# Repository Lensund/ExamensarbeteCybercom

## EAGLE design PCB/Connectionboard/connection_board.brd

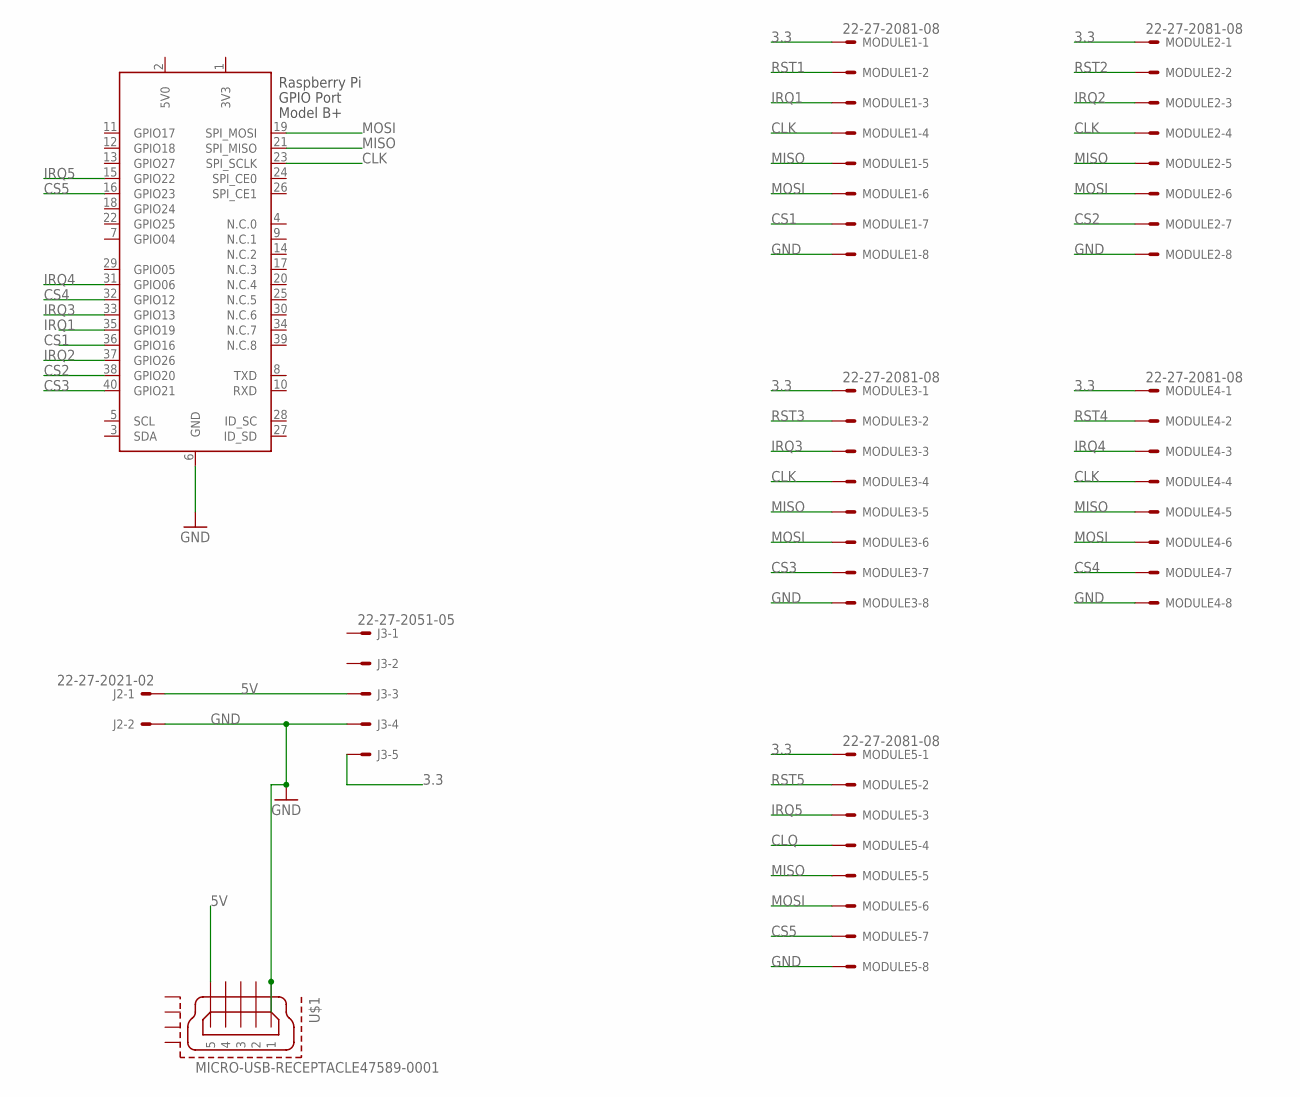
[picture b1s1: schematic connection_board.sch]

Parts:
J2: 22-27-2021-02; 6410-02
J3: 22-27-2051-05; 6410-05
MODULE1, MODULE2, MODULE3, MODULE4, MODULE5: 22-27-2081-08; 6410-08
U$1: MICRO-USB-RECEPTACLE47589-0001; 47589-0001
X1: RASPI_BOARD_B+_E0; RASPI_BOARD_B+_EDGES_0DRILL

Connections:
3.3: J3.5, MODULE1.1, MODULE2.1, MODULE3.1, MODULE4.1, MODULE5.1
3V3: X1.1 (3V3)
5V: J2.1, J3.3, U$1.5
5V0: X1.2 (5V0)
CLK: MODULE1.4, MODULE2.4, MODULE3.4, MODULE4.4, X1.23 (SPI_SCLK)
CLQ: MODULE5.4
CS1: MODULE1.7, X1.36 (GPIO16)
CS2: MODULE2.7, X1.38 (GPIO20)
CS3: MODULE3.7, X1.40 (GPIO21)
CS4: MODULE4.7, X1.32 (GPIO12)
CS5: MODULE5.7, X1.16 (GPIO23)
GND: J2.2, J3.4, MODULE1.8, MODULE2.8, MODULE3.8, MODULE4.8, MODULE5.8, U$1.1, X1.6 (GND)
IRQ1: MODULE1.3, X1.35 (GPIO19)
IRQ2: MODULE2.3, X1.37 (GPIO26)
IRQ3: MODULE3.3, X1.33 (GPIO13)
IRQ4: MODULE4.3, X1.31 (GPIO06)
IRQ5: MODULE5.3, X1.15 (GPIO22)
MISO: MODULE1.5, MODULE2.5, MODULE3.5, MODULE4.5, MODULE5.5, X1.21 (SPI_MISO)
MOSI: MODULE1.6, MODULE2.6, MODULE3.6, MODULE4.6, MODULE5.6, X1.19 (SPI_MOSI)
RST1: MODULE1.2
RST2: MODULE2.2
RST3: MODULE3.2
RST4: MODULE4.2
RST5: MODULE5.2

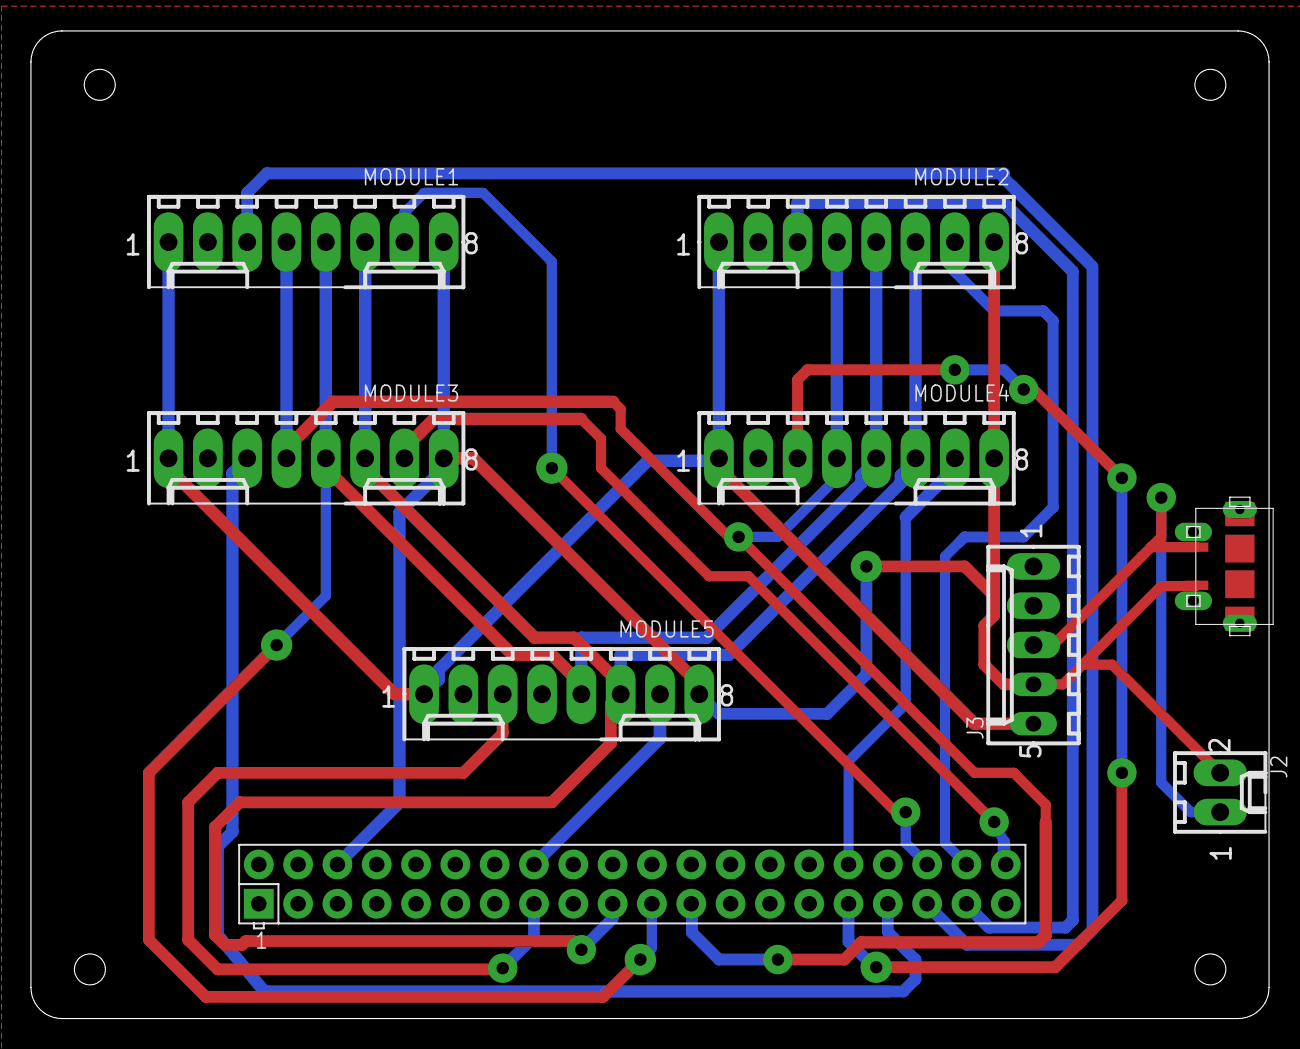
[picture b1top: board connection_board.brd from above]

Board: 2 copper layers, 80.0 x 63.8 mm, 9 parts (0 on the bottom side), 16 nets.

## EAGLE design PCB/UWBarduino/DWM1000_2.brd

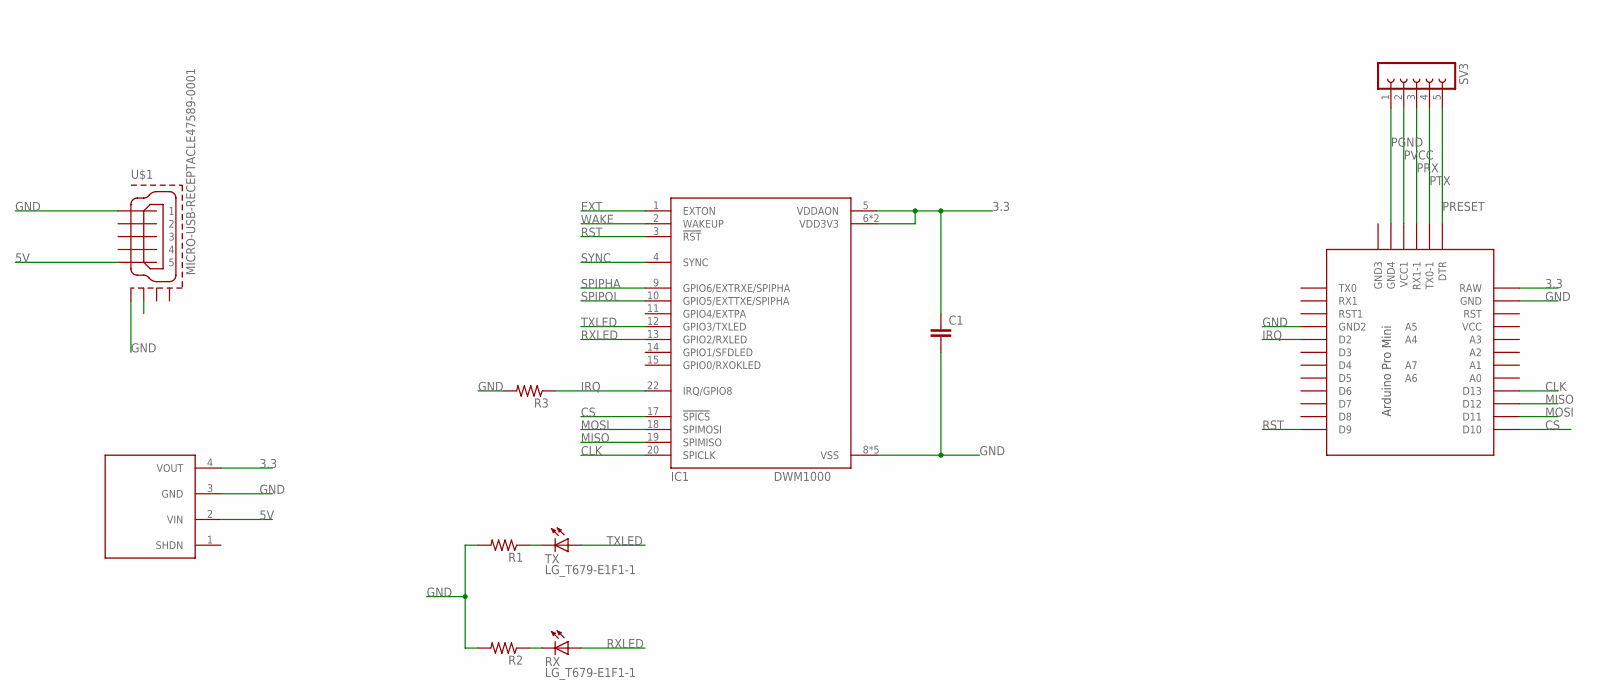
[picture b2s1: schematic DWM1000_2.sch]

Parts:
C1: CC1206; C1206
IC1: DWM1000
R1, R2, R3: R-US_M0805; M0805
RX: LG_T679-E1F1-1; PLCC2
SV3: FE05-1
TX: LG_T679-E1F1-1; PLCC2
U$1: MICRO-USB-RECEPTACLE47589-0001; 47589-0001
U$2: PRO-MINI-2
U$3: D24V5F3

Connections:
3.3: C1.1, IC1.5 (VDDAON), IC1.6 (VDD3V3), IC1.7 (VDD3V3), U$2.RAW, U$3.4 (VOUT)
5V: U$1.5, U$3.2 (VIN)
CLK: IC1.20 (SPICLK), U$2.D13
CS: IC1.17 (!SPICS), U$2.D10
EXT: IC1.1 (EXTON)
GND: C1.2, IC1.8 (VSS), IC1.16 (VSS), IC1.21 (VSS), IC1.23 (VSS), IC1.24 (VSS), R1.2, R2.2, R3.2, U$1.1, U$1.CASING1 (GND1), U$2.GND, U$2.GND1 (GND2), U$3.3 (GND)
IRQ: IC1.22 (IRQ/GPIO8), R3.1, U$2.D2
MISO: IC1.19 (SPIMISO), U$2.D12
MOSI: IC1.18 (SPIMOSI), U$2.D11
unnamed: R1.1, TX.C
unnamed: R2.1, RX.C
PGND: SV3.1, U$2.GND3 (GND4)
PRESET: SV3.5, U$2.DTR
PRX: SV3.3, U$2.RX1-1
PTX: SV3.4, U$2.TX0-1
PVCC: SV3.2, U$2.VCC1
RST: IC1.3 (!RST), U$2.D9
RXLED: IC1.13 (GPIO2/RXLED), RX.A
SPIPHA: IC1.9 (GPIO6/EXTRXE/SPIPHA)
SPIPOL: IC1.10 (GPIO5/EXTTXE/SPIPHA)
SYNC: IC1.4 (SYNC)
TXLED: IC1.12 (GPIO3/TXLED), TX.A
WAKE: IC1.2 (WAKEUP)

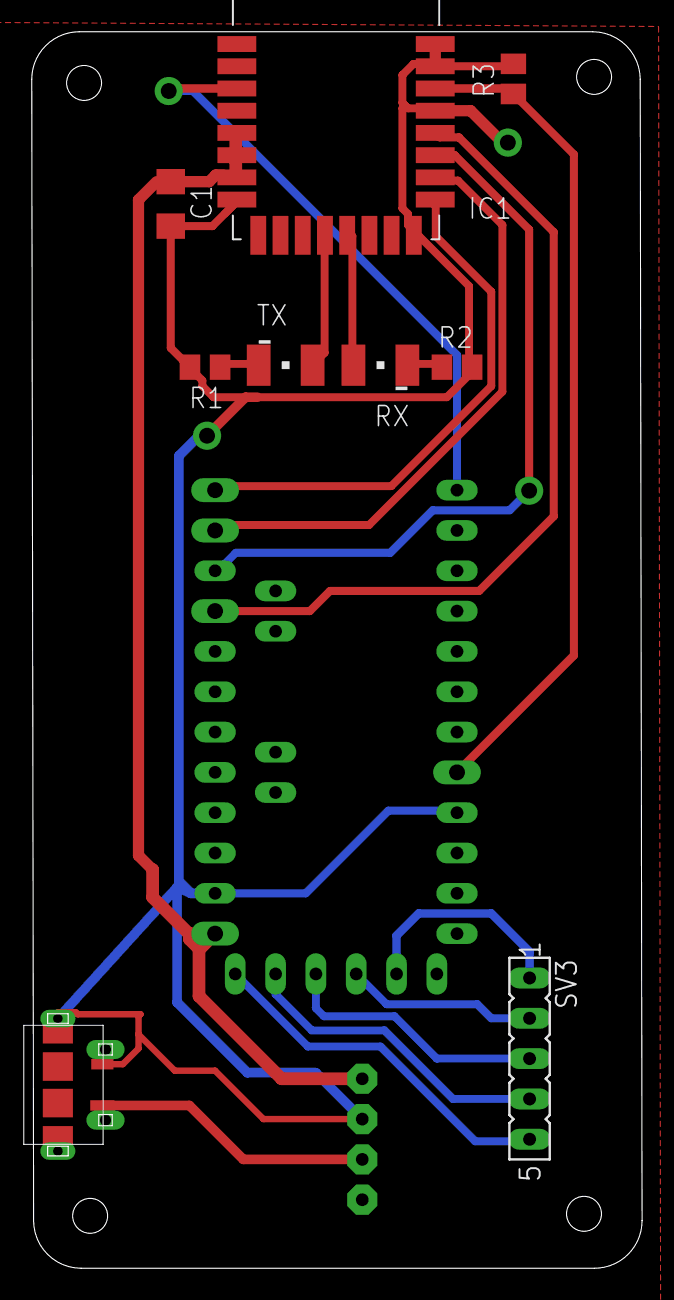
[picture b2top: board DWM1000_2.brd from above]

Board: 2 copper layers, 38.5 x 77.9 mm, 11 parts (0 on the bottom side), 18 nets.

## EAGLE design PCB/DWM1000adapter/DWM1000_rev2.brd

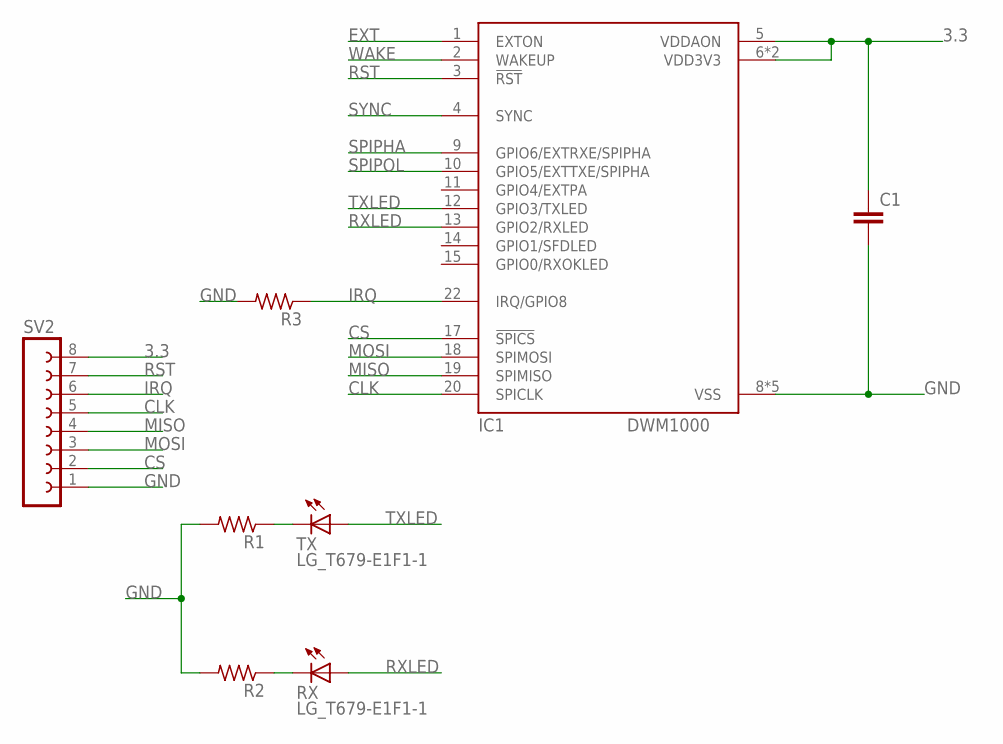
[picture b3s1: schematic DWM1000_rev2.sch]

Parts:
C1: CC1206; C1206
IC1: DWM1000
R1, R2, R3: R-US_M0805; M0805
RX: LG_T679-E1F1-1; PLCC2
SV2: FE08-1; FE08
TX: LG_T679-E1F1-1; PLCC2

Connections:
3.3: C1.1, IC1.5 (VDDAON), IC1.6 (VDD3V3), IC1.7 (VDD3V3), SV2.8
CLK: IC1.20 (SPICLK), SV2.5
CS: IC1.17 (!SPICS), SV2.2
EXT: IC1.1 (EXTON)
GND: C1.2, IC1.8 (VSS), IC1.16 (VSS), IC1.21 (VSS), IC1.23 (VSS), IC1.24 (VSS), R1.2, R2.2, R3.2, SV2.1
IRQ: IC1.22 (IRQ/GPIO8), R3.1, SV2.6
MISO: IC1.19 (SPIMISO), SV2.4
MOSI: IC1.18 (SPIMOSI), SV2.3
unnamed: R1.1, TX.C
unnamed: R2.1, RX.C
RST: IC1.3 (!RST), SV2.7
RXLED: IC1.13 (GPIO2/RXLED), RX.A
SPIPHA: IC1.9 (GPIO6/EXTRXE/SPIPHA)
SPIPOL: IC1.10 (GPIO5/EXTTXE/SPIPHA)
SYNC: IC1.4 (SYNC)
TXLED: IC1.12 (GPIO3/TXLED), TX.A
WAKE: IC1.2 (WAKEUP)

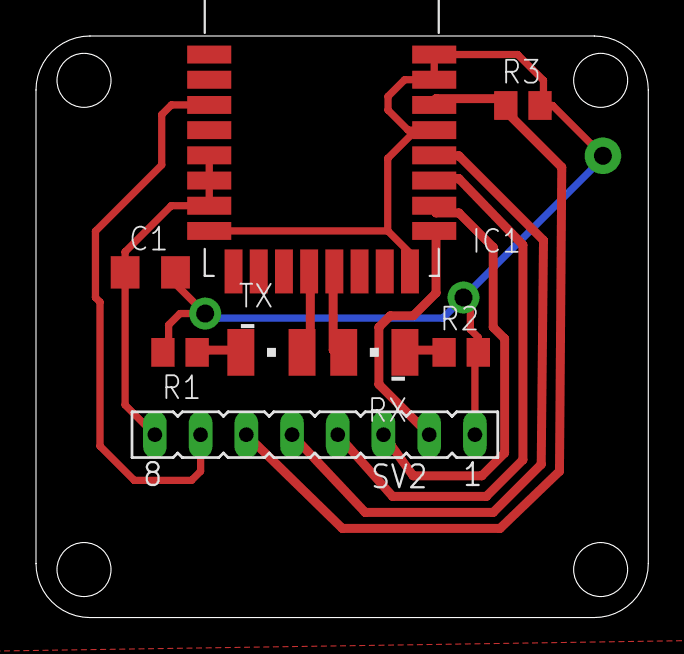
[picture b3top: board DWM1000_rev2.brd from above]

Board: 2 copper layers, 34.0 x 32.3 mm, 8 parts (0 on the bottom side), 12 nets.

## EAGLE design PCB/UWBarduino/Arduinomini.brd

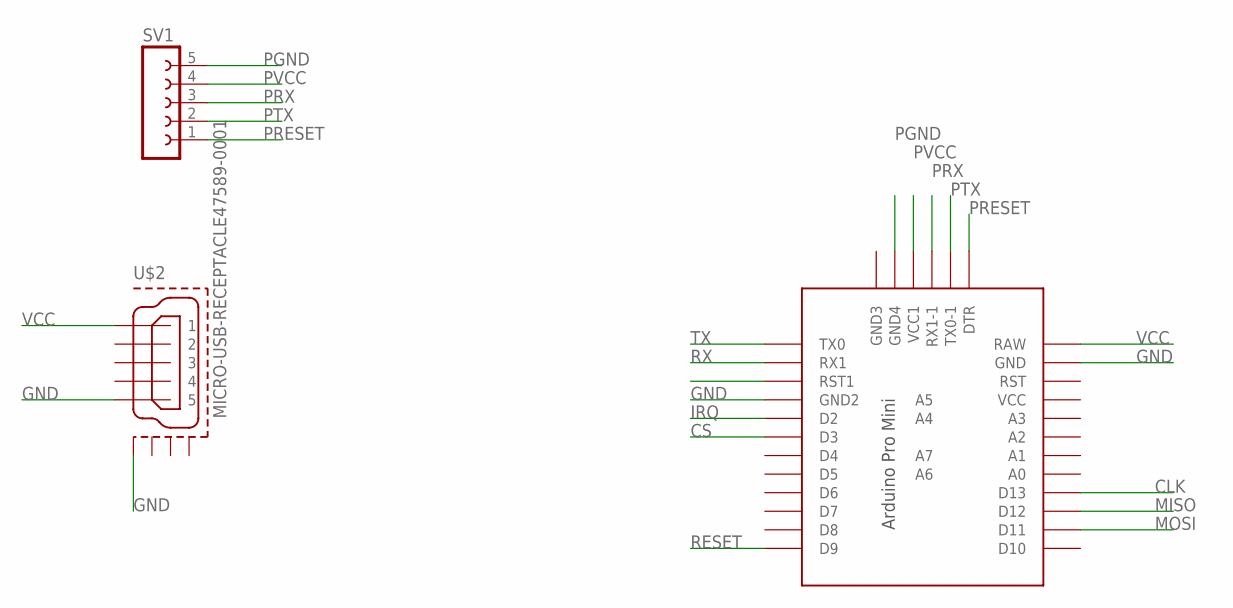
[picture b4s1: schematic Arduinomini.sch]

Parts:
SV1: FE05-1
U$1: PRO-MINI-2
U$2: MICRO-USB-RECEPTACLE47589-0001; 47589-0001

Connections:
CLK: U$1.D13
CS: U$1.D3
GND: U$1.GND, U$1.GND1 (GND2), U$2.5, U$2.CASING1 (GND1)
IRQ: U$1.D2
MISO: U$1.D12
MOSI: U$1.D11
PGND: SV1.5, U$1.GND3 (GND4)
PRESET: SV1.1, U$1.DTR
PRX: SV1.3, U$1.RX1-1
PTX: SV1.2, U$1.TX0-1
PVCC: SV1.4, U$1.VCC1
RESET: U$1.D9
RX: U$1.RX1
TX: U$1.TX0
VCC: U$1.RAW, U$2.1

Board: 2 copper layers, 3 parts (0 on the bottom side), 7 nets, no tracks yet.

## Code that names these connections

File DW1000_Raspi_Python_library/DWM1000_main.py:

#Dis tha main

import DW1000
import monotonic
import DW1000Constants as C
import rospy

from DW1000RangingAnchor_class import *

#Define RPi output pins for the UWB modules
CS1 = 16
CS2 = 20
CS3 = 21
CS4 = 12
CS5 = 23
IRQ1 = 19
IRQ2 = 26
IRQ3 = 13
IRQ4 = 6
IRQ5 = 22
#DWM1000_module1 = DWM1000_ranging("module1", "82:17:5B:D5:A9:9A:E2:1A", CS1, IRQ1)
#DWM1000_module2 = DWM1000_ranging("module2", "82:17:5B:D5:A9:9A:E2:2A", CS2, IRQ2)
#DWM1000_module3 = DWM1000_ranging("module3", "82:17:5B:D5:A9:9A:E2:3A", CS3, IRQ3)
#DWM1000_module4 = DWM1000_ranging("module4", "82:17:5B:D5:A9:9A:E2:4A", CS4, IRQ4)

#Add 5th module if applied
DWM1000_module5 = DWM1000_ranging("module5", "82:17:5B:D5:A9:9A:E2:5A", CS5, IRQ5)

def das_loop():
    #Loop for calculating the range
    rangemodule1_old = None
    test = True
    while test:
        range_module1 = DWM1000_module5.loop()
        if range_module1 != None:
            #rangemodule1_old = range_module1
            test = False

    #range_module2 = DWM1000_module.loop()
    #range_module3 = DWM1000_module.loop()
    #range_module4 = DWM1000_module.loop()
    print('Range module 5: %.3f' %(range_module1))






    #except KeyboardInterrupt:
        #DW1000.close()


def main():
    try:
        while 1:
            das_loop()
    except KeyboardInterrupt:
        print('    Interrupted by user')


if __name__ == '__main__':
#Run the main loop.
    main()

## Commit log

2018-01-30 README.md
2018-01-30 sample.txt
2018-01-30 ExamensarbeteCybercom
2018-01-30 folder removal
2018-01-30 test
2018-01-31 rm ExamensarbeteCybercom/ -rf
2018-02-01 test igen
2018-02-01 Movin some files
2018-02-02 matlab code1
2018-02-08 Matlab file
2018-02-08 test2
2018-02-09 reset
2018-02-09 LFS test
2018-02-09 git ignore
2018-02-16 Implementation Friday
2018-02-19 Matulabbu
2018-02-23 added pcb files and matlab config
2018-03-01 knas
2018-03-02 added some stuff
2018-03-05 added dw100 stuff
2018-03-07 comment max speed
2018-03-08 new day new opportunities
2018-03-08 ROS stuff
2018-03-08 testing ros
2018-03-08 moa ros
2018-03-08 some pcb

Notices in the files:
parts and their libraries:
con-molex-usb: (C) 2014 Tomasz Boleslaw CEDRO, cederom@tlen.pl, http://www.tomek.cedro.info.
